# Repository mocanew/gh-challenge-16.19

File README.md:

# gh-challenge-16.19
This is a Capture the Flag type challenge part of the GoHard platform that has a reward in Prey which you can exchange for loot - electronic components. To participate you must first finish the basic challenges and become a Wolf! Read all about it on the website https://gohard.inventeaza.ro/ . GoHard!

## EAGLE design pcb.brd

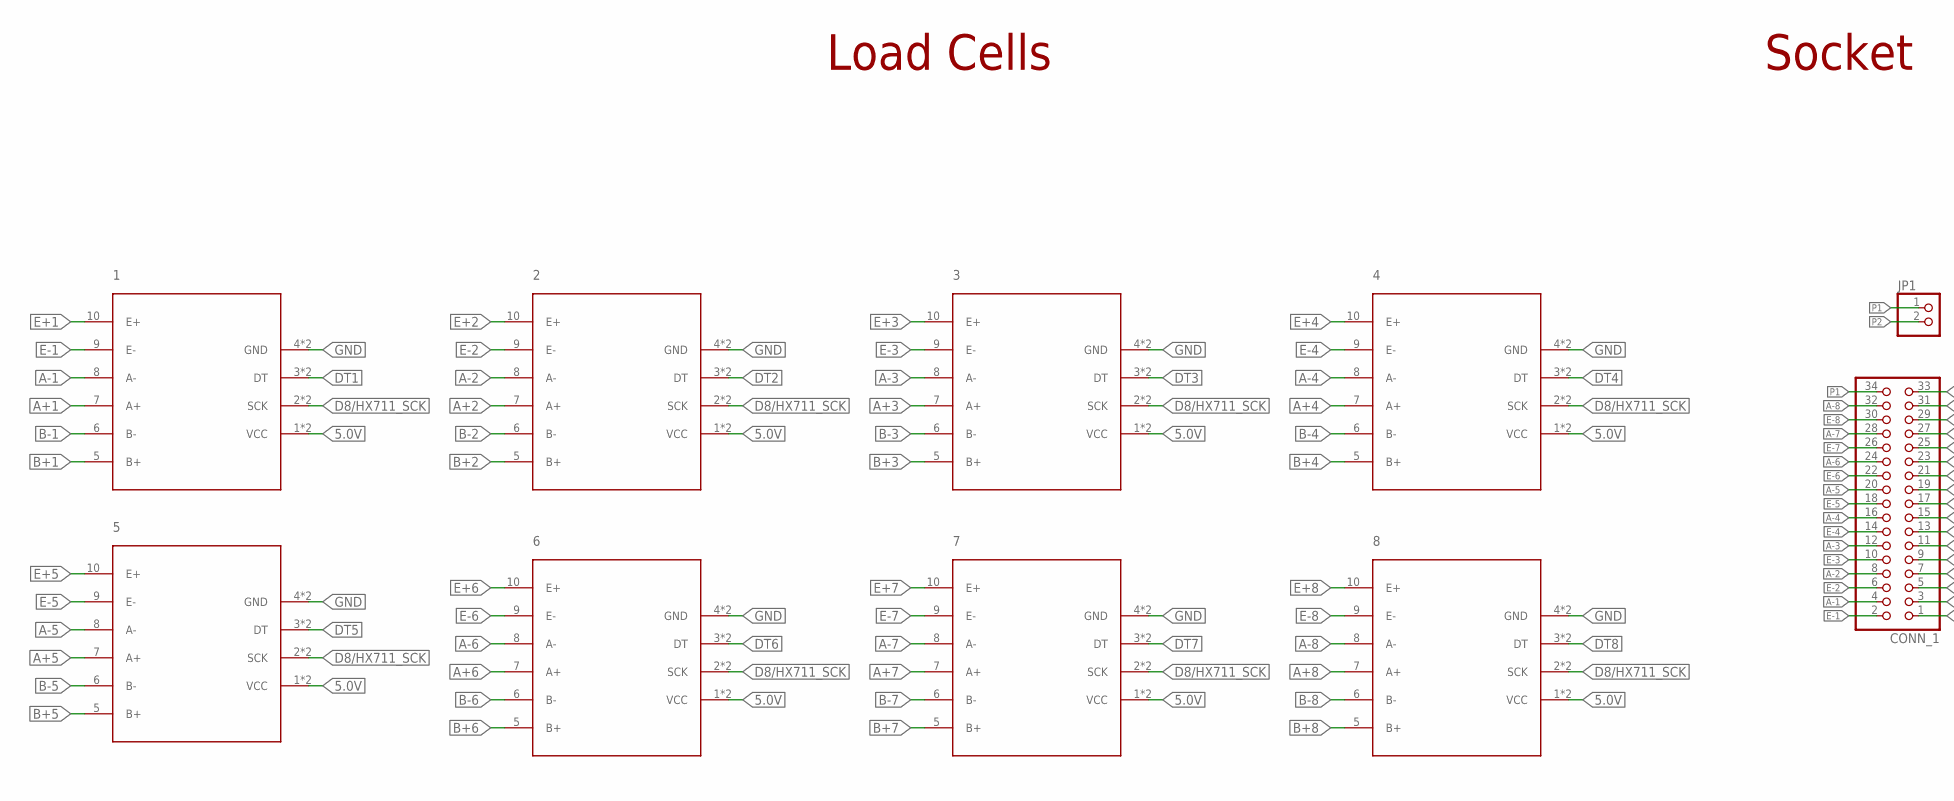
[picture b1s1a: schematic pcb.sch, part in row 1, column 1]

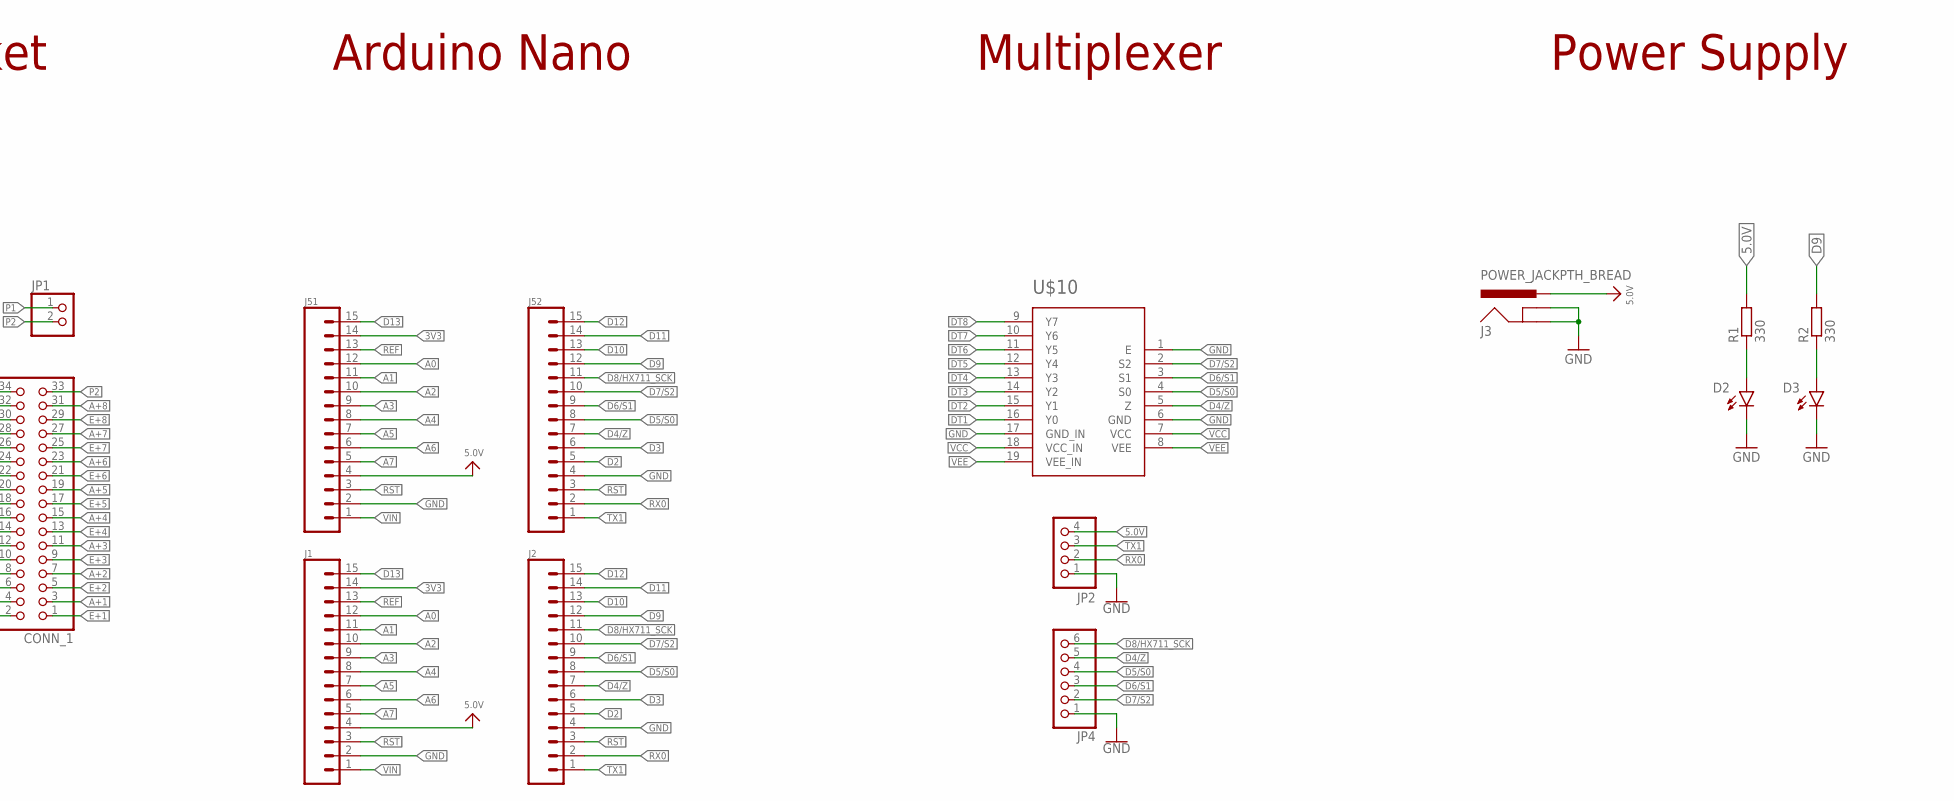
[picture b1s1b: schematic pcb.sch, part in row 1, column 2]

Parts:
1, 2, 3, 4, 5, 6, 7, 8: HX711
CONN_1: PINHD-2X17; 2X17
D2, D3: LED5MM; LED_5MM
J1, J2, J51, J52: CONN_15; 1X15
J3: POWER_JACKPTH_BREAD; POWER_JACK_PTH_BREAD
JP1: PINHD-1X2; 1X02
JP2: PINHD-1X4/90; 1X04/90
JP4: PINHD-1X6/90; 1X06/90
R1, R2: 330; 0204/7
U$10: 8CHMPLEX; 74HC4051

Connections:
3V3: J1.14, J51.14
5.0V: 1.1 (VCC), 1.1.2 (VCC), 2.1 (VCC), 2.1.2 (VCC), 3.1 (VCC), 3.1.2 (VCC), 4.1 (VCC), 4.1.2 (VCC), 5.1 (VCC), 5.1.2 (VCC), 6.1 (VCC), 6.1.2 (VCC), 7.1 (VCC), 7.1.2 (VCC), 8.1 (VCC), 8.1.2 (VCC), J1.4, J3.PWR, J51.4, JP2.4, R1.2
A0: J1.12, J51.12
A1: J1.11, J51.11
A2: J1.10, J51.10
A3: J1.9, J51.9
A4: J1.8, J51.8
A5: J1.7, J51.7
A6: J1.6, J51.6
A7: J1.5, J51.5
A+1: 1.7 (A+), CONN_1.3
A+2: 2.7 (A+), CONN_1.7
A+3: 3.7 (A+), CONN_1.11
A+4: 4.7 (A+), CONN_1.15
A+5: 5.7 (A+), CONN_1.19
A+6: 6.7 (A+), CONN_1.23
A+7: 7.7 (A+), CONN_1.27
A+8: 8.7 (A+), CONN_1.31
A-1: 1.8 (A-), CONN_1.4
A-2: 2.8 (A-), CONN_1.8
A-3: 3.8 (A-), CONN_1.12
A-4: 4.8 (A-), CONN_1.16
A-5: 5.8 (A-), CONN_1.20
A-6: 6.8 (A-), CONN_1.24
A-7: 7.8 (A-), CONN_1.28
A-8: 8.8 (A-), CONN_1.32
B+1: 1.5 (B+)
B+2: 2.5 (B+)
B+3: 3.5 (B+)
B+4: 4.5 (B+)
B+5: 5.5 (B+)
B+6: 6.5 (B+)
B+7: 7.5 (B+)
B+8: 8.5 (B+)
B-1: 1.6 (B-)
B-2: 2.6 (B-)
B-3: 3.6 (B-)
B-4: 4.6 (B-)
B-5: 5.6 (B-)
B-6: 6.6 (B-)
B-7: 7.6 (B-)
B-8: 8.6 (B-)
D2: J2.5, J52.5
D3: J2.6, J52.6
D4/Z: J2.7, J52.7, JP4.5, U$10.5 (Z)
D5/S0: J2.8, J52.8, JP4.4, U$10.4 (S0)
D6/S1: J2.9, J52.9, JP4.3, U$10.3 (S1)
D7/S2: J2.10, J52.10, JP4.2, U$10.2 (S2)
D8/HX711_SCK: 1.2 (SCK), 1.2.2 (SCK), 2.2 (SCK), 2.2.2 (SCK), 3.2 (SCK), 3.2.2 (SCK), 4.2 (SCK), 4.2.2 (SCK), 5.2 (SCK), 5.2.2 (SCK), 6.2 (SCK), 6.2.2 (SCK), 7.2 (SCK), 7.2.2 (SCK), 8.2 (SCK), 8.2.2 (SCK), J2.11, J52.11, JP4.6
D9: J2.12, J52.12, R2.2
D10: J2.13, J52.13
D11: J2.14, J52.14
D12: J2.15, J52.15
D13: J1.15, J51.15
DT1: 1.3 (DT), 1.3.2 (DT), U$10.16 (Y0)
DT2: 2.3 (DT), 2.3.2 (DT), U$10.15 (Y1)
DT3: 3.3 (DT), 3.3.2 (DT), U$10.14 (Y2)
DT4: 4.3 (DT), 4.3.2 (DT), U$10.13 (Y3)
DT5: 5.3 (DT), 5.3.2 (DT), U$10.12 (Y4)
DT6: 6.3 (DT), 6.3.2 (DT), U$10.11 (Y5)
DT7: 7.3 (DT), 7.3.2 (DT), U$10.10 (Y6)
DT8: 8.3 (DT), 8.3.2 (DT), U$10.9 (Y7)
E+1: 1.10 (E+), CONN_1.1
E+2: 2.10 (E+), CONN_1.5
E+3: 3.10 (E+), CONN_1.9
E+4: 4.10 (E+), CONN_1.13
E+5: 5.10 (E+), CONN_1.17
E+6: 6.10 (E+), CONN_1.21
E+7: 7.10 (E+), CONN_1.25
E+8: 8.10 (E+), CONN_1.29
E-1: 1.9 (E-), CONN_1.2
E-2: 2.9 (E-), CONN_1.6
E-3: 3.9 (E-), CONN_1.10
E-4: 4.9 (E-), CONN_1.14
E-5: 5.9 (E-), CONN_1.18
E-6: 6.9 (E-), CONN_1.22
E-7: 7.9 (E-), CONN_1.26
E-8: 8.9 (E-), CONN_1.30
GND: 1.4 (GND), 1.4.2 (GND), 2.4 (GND), 2.4.2 (GND), 3.4 (GND), 3.4.2 (GND), 4.4 (GND), 4.4.2 (GND), 5.4 (GND), 5.4.2 (GND), 6.4 (GND), 6.4.2 (GND), 7.4 (GND), 7.4.2 (GND), 8.4 (GND), 8.4.2 (GND), D2.K (C), D3.K (C), J1.2, J2.4, J3.GND, J3.GNDBREAK, J51.2, J52.4, JP2.1, JP4.1, U$10.1 (E), U$10.6 (GND), U$10.17 (GND_IN)
unnamed: D2.A, R1.1
unnamed: D3.A, R2.1
P1: CONN_1.34, JP1.1
P2: CONN_1.33, JP1.2
REF: J1.13, J51.13
RST: J1.3, J2.3, J51.3, J52.3
RX0: J2.2, J52.2, JP2.2
TX1: J2.1, J52.1, JP2.3
VCC: U$10.7 (VCC), U$10.18 (VCC_IN)
VEE: U$10.8 (VEE), U$10.19 (VEE_IN)
VIN: J1.1, J51.1

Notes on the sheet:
Load Cells
Multiplexer
Arduino Nano
Power Supply
Socket

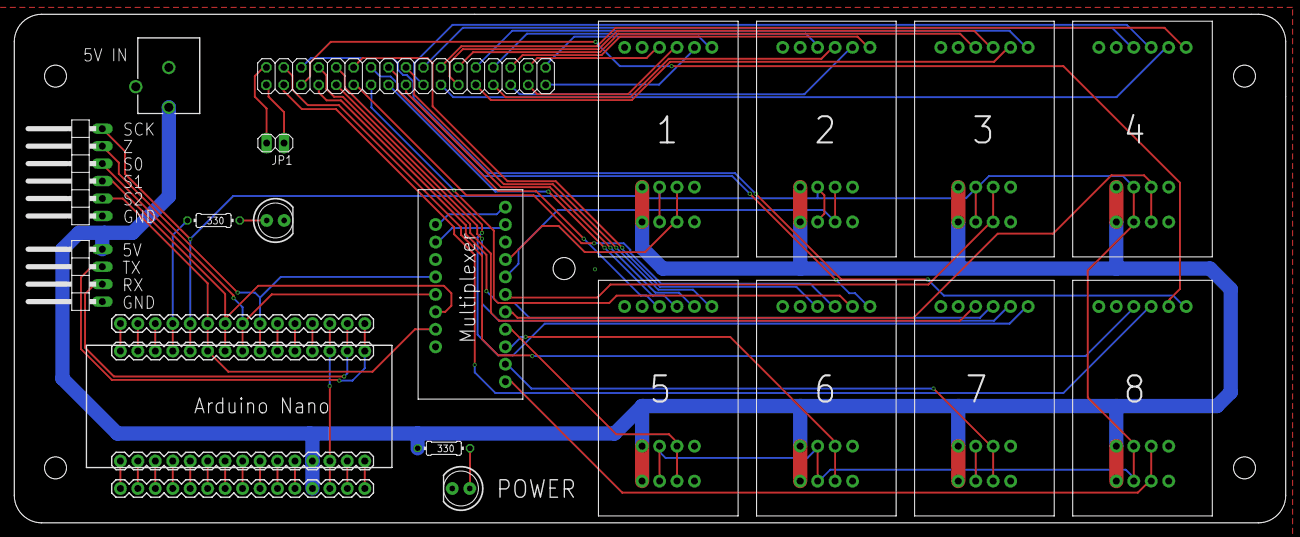
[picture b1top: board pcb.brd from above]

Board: 2 copper layers, 185.0 x 74.0 mm, 22 parts (0 on the bottom side), 74 nets.

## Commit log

2021-02-04 resources
2021-10-07 Modified design so that it respects the height constraint

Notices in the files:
parts and their libraries:
SparkFun-Connectors: Licensing: Creative Commons ShareAlike 4.0 International - https://creativecommons.org/licenses/by-sa/4.0
microbuilder: This work is placed in the public domain, and may be freely used for commercial and non-commercial work with the following conditions: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
